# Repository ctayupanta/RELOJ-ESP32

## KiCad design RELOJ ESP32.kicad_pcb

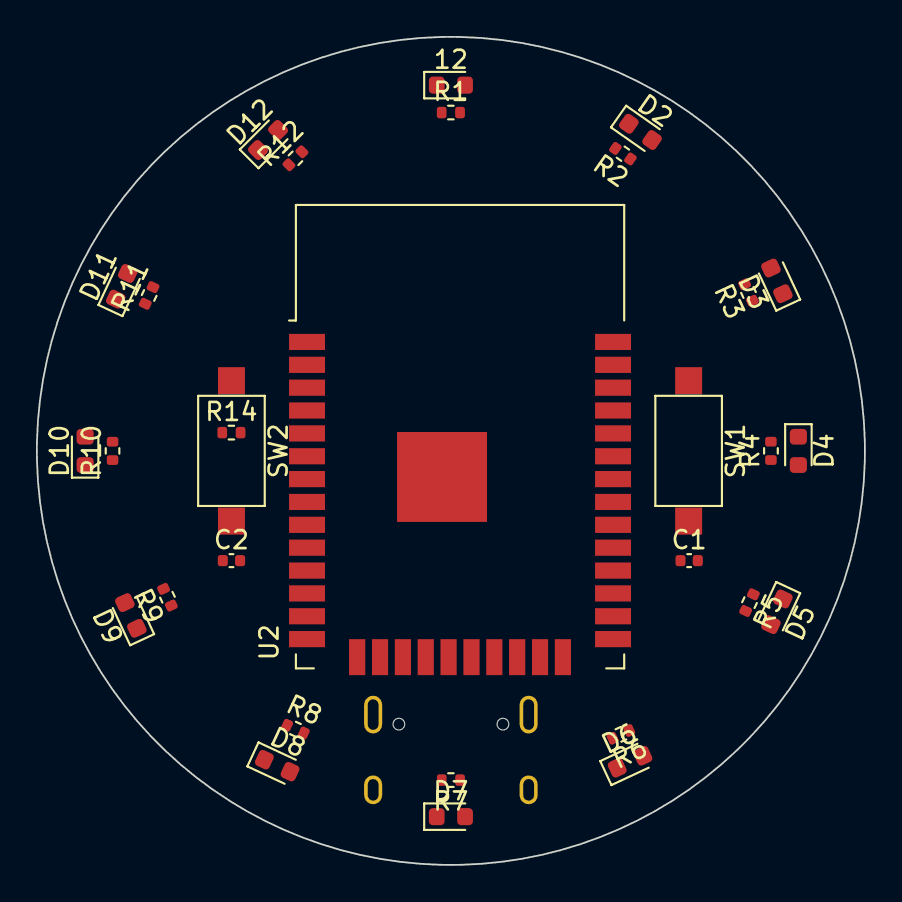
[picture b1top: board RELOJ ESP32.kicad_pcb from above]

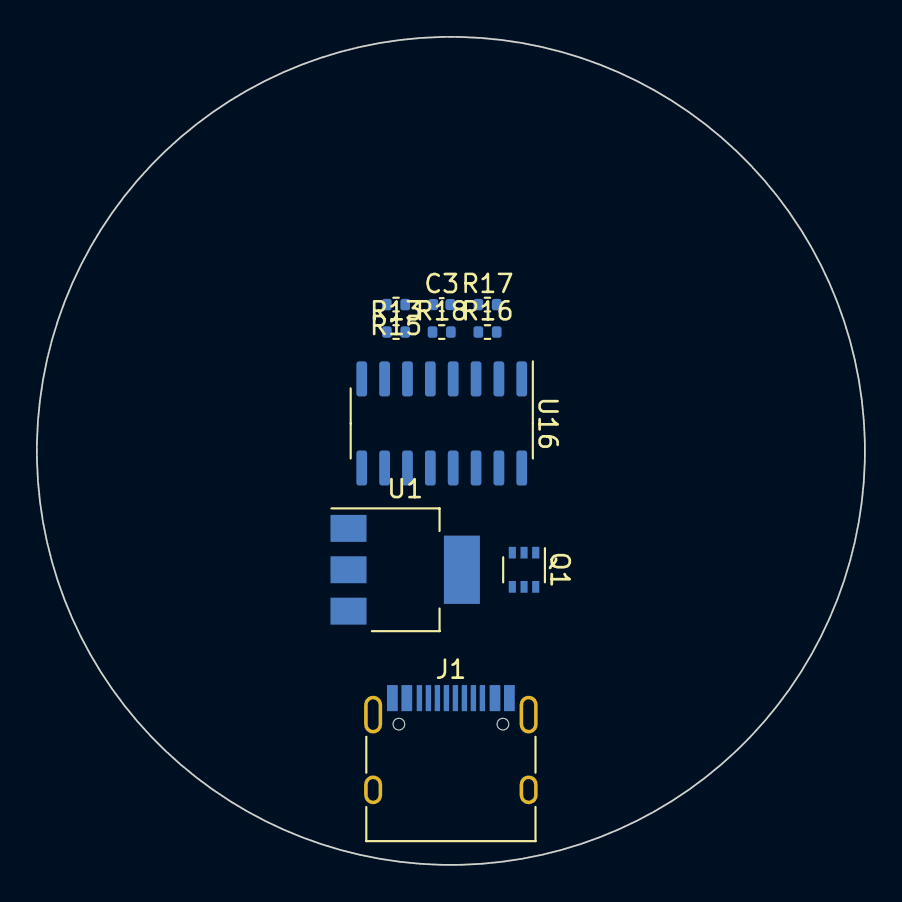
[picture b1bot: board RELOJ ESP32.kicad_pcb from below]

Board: 2 copper layers, 46.0 x 46.0 mm, 40 parts (10 on the bottom side), 37 nets, no tracks yet.

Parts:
12: LED; LED_0603_1608Metric
C1: 10uf; C_0402_1005Metric
C2: 100nf; C_0402_1005Metric
C3: 100nF; C_0402_1005Metric
D2, D3, D4, D5, D6, D7, D8, D9, D10, D11, D12: LED; LED_0603_1608Metric
J1: USB_C_Receptacle_USB2.0; USB_C_Receptacle_HRO_TYPE-C-31-M-12
Q1: PMBT3904YS; SOT-363_SC-70-6
R1, R2, R3, R4, R5, R6, R7, R8, R9, R10, R11, R12: R; R_0402_1005Metric
R13, R15, R16, R17, R18: 1k; R_0402_1005Metric
R14: 10k; R_0402_1005Metric
SW1, SW2: SW_Push; SW_SPST_CK_RS282G05A3
U1: LD1117S33TR_SOT223; SOT-223-3_TabPin2
U2: ESP32-WROOM-32D; ESP32-WROOM-32
U16: CH340C; SOIC-16_3.9x9.9mm_P1.27mm

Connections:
3.3v: C2.1, U1.2 (VO), U2.2 (VDD)
5v: C1.1, J1.A4 (VBUS), J1.A9 (VBUS), J1.B4 (VBUS), J1.B9 (VBUS), U1.3 (VI), U16.16 (VCC)
-5v: C1.2, C2.2, U1.1 (GND)
D+: J1.A6 (D+), U16.5 (UD+)
D-: J1.A7 (D-), U16.6 (UD-)
DTR: Q1.1 (E1), R15.1, U16.13 (~DTR)
EN: Q1.4 (E2), R14.1, SW1.2, U2.3 (EN)
GND: C3.1, J1.A1 (GND), J1.A12 (GND), J1.B1 (GND), J1.B12 (GND), J1.S1 (SHIELD), R1.1, R2.1, R3.1, R4.1, R5.1, R6.1, R7.1, R8.1, R9.1, R10.1, R11.1, R12.1, SW1.1, SW2.1, U2.1 (GND), U2.15 (GND), U2.38 (GND), U2.39 (GND), U16.1 (GND)
IO0: Q1.6 (C1), R13.2, SW2.2, U2.25 (IO0)
IO5: 12.2 (A), U2.29 (IO5)
IO12: D2.2 (A), U2.14 (IO12)
IO13: D3.2 (A), U2.16 (IO13)
IO14: D4.2 (A), U2.13 (IO14)
IO15: D5.2 (A), U2.23 (IO15)
IO16: D6.2 (A), U2.27 (IO16)
IO17: D7.2 (A), U2.28 (IO17)
IO18: D8.2 (A), U2.30 (IO18)
IO19: D9.2 (A), U2.31 (IO19)
IO21: D10.2 (A), U2.33 (IO21)
IO22: D11.2 (A), U2.36 (IO22)
IO23: D12.2 (A), U2.37 (IO23)
unnamed: 12.1 (K), R1.2
unnamed: D2.1 (K), R2.2
unnamed: D3.1 (K), R3.2
unnamed: D4.1 (K), R4.2
unnamed: D5.1 (K), R5.2
unnamed: D6.1 (K), R6.2
unnamed: D7.1 (K), R7.2
unnamed: D8.1 (K), R8.2
unnamed: D9.1 (K), R9.2
unnamed: D10.1 (K), R10.2
unnamed: D11.1 (K), R11.2
unnamed: D12.1 (K), R12.2
unnamed: Q1.2 (B1), R16.2
unnamed: Q1.5 (B2), R15.2
RTS: Q1.3 (C2), R16.1, U16.14 (~RTS)
VCC: R13.1, R14.2

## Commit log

2022-09-10 Reloj Esp
